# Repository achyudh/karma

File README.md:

# Karma

Karma is a 36-key wireless split ergonomic mechanical keyboard inspired by two very popular ergonomic keyboards: [Corne](https://github.com/foostan/crkbd) and [TOTEM](https://github.com/GEIGEIGEIST/TOTEM).

## Features

- **Ergonomic 36-key layout**: A compact layout with 3x5 column-staggered keys, plus 3 thumb keys for each side.
- **Wireless first**: Prioritizes a wireless split setup but can be used partially-wired by connecting the central side using USB-C.
- **Low-profile design**: Engineered for a sleek, low-profile build that allows your palms to rest comfortably on the table while typing. This is achieved through the use of Kailh Choc switches and recessed cutouts for hot-swap sockets, reducing the overall case height (similar to the TOTEM keyboard), and using 1mm EVA foam instead of rubber feet.
- **Exceptional battery life**: Has a battery life that is measured in weeks, not days.

### Firmware

The Karma keyboard supports the [ZMK](https://zmk.dev/) open-source firmware. You can find my ZMK configuration for this keyboard in [this repo](https://github.com/achyudh/karma-zmk).

## Build Guide

### Bill of Materials

To build the Karma keyboard, you'll need the following components:

| Part Name                               | Qty    | Remarks   |
| --------------------------------------- |:------:| --------- |
| 2x SEEED XIAO BLE microcontrollers      | 2      |           |
| Kailh Choc V1 low-profile switches      | 36     | Low-profile mechanical switches |
| Keycaps compatible with Kailh Choc V1   | 36     | MX-spaced keycaps are preferred for better fit |
| Hotswap sockets for Kailh Choc V1       | 36     |           |
| SOD123 diodes                           | 36     |           |
| JST PH 2-pin SMD Header                 | 2      |           |
| 301230 LiPo Batteries                   | 2      | Only 1 required for partially wired build |
| 3D-printed case                         | 2      |           |
| M2 screws (5mm length)                  | 8      |           |
| M2 heat-set inserts (2mm height)        | 8      |           |
| Self-adhesive EVA foam (1mm)            | -      | A slimmer alternative to rubber feet |

### Assembly

**1. Order the Components**
- Zip up the gerber files for the [left side](./mk1/pcb-left/pcb-left-gerbers/) and the [right side](./mk1/pcb-right/pcb-right-gerbers/).
- Order the PCBs from a PCB prototype manufacturer like JLCPCB.
- 3D print the STL files for the case in [this repo](./mk1/enclosure/).
- All the other components are generic and can be found in Aliexpress.

**2. Solder the Diodes**
- Solder the SOD123 diodes to the top of the PCB, paying attention to the polarity.
- Apply solder to one pad, place the diode, and reflow the solder. Then solder the second pad.

**3. Install the Hotswap Sockets**
- Solder hotswap sockets in place by first securing one pad, then ensuring they are properly seated before soldering the second pad.

**4. Microcontroller Installation**
- Flash the firmware onto the SEEED XIAO BLE microcontrollers before soldering them to the PCB.
- Place the microcontroller in the designated spot and solder the pads, starting with the corners to secure it, then solder the rest.

**5. Connect the Batteries**
- Solder the JST PH 2-pin SMD Header to the PCB.
- Check the polarity of the battery with a multimeter and connect the batteries to the JST header such that the red wire is connected to the positive (+) pad and the black wire to the negative (-) pad on the PCB.

**6. Mount the Case**
- Insert M2 heat-set inserts into the screw holes in the 3D-printed case.
- Place the PCB inside the case, ensuring the microcontroller and battery fit snugly.
- Attach the two halves of the case using the M2 screws, securing them tightly.

**7. Install the Keycaps and Switches**
- Insert the Kailh Choc V1 switches into the hotswap sockets, ensuring they click into place.
- Attach your keycaps to the switches.

**8. Add EVA Foam**
- Cut and apply self-adhesive EVA foam to the bottom of the case for added grip and cushioning.

**9. Final steps**
- Once assembled, test the keyboard to ensure all switches and connections work.
- If necessary, adjust the [ZMK](https://zmk.dev/) firmware for your specific keymap.

Congratulations! You've completed your Karma keyboard build.

## License

This project is open-source and licensed under the CERN Open Hardware Licence Version 2 - Strongly Reciprocal License. See the [LICENSE](./LICENSE) file for details.

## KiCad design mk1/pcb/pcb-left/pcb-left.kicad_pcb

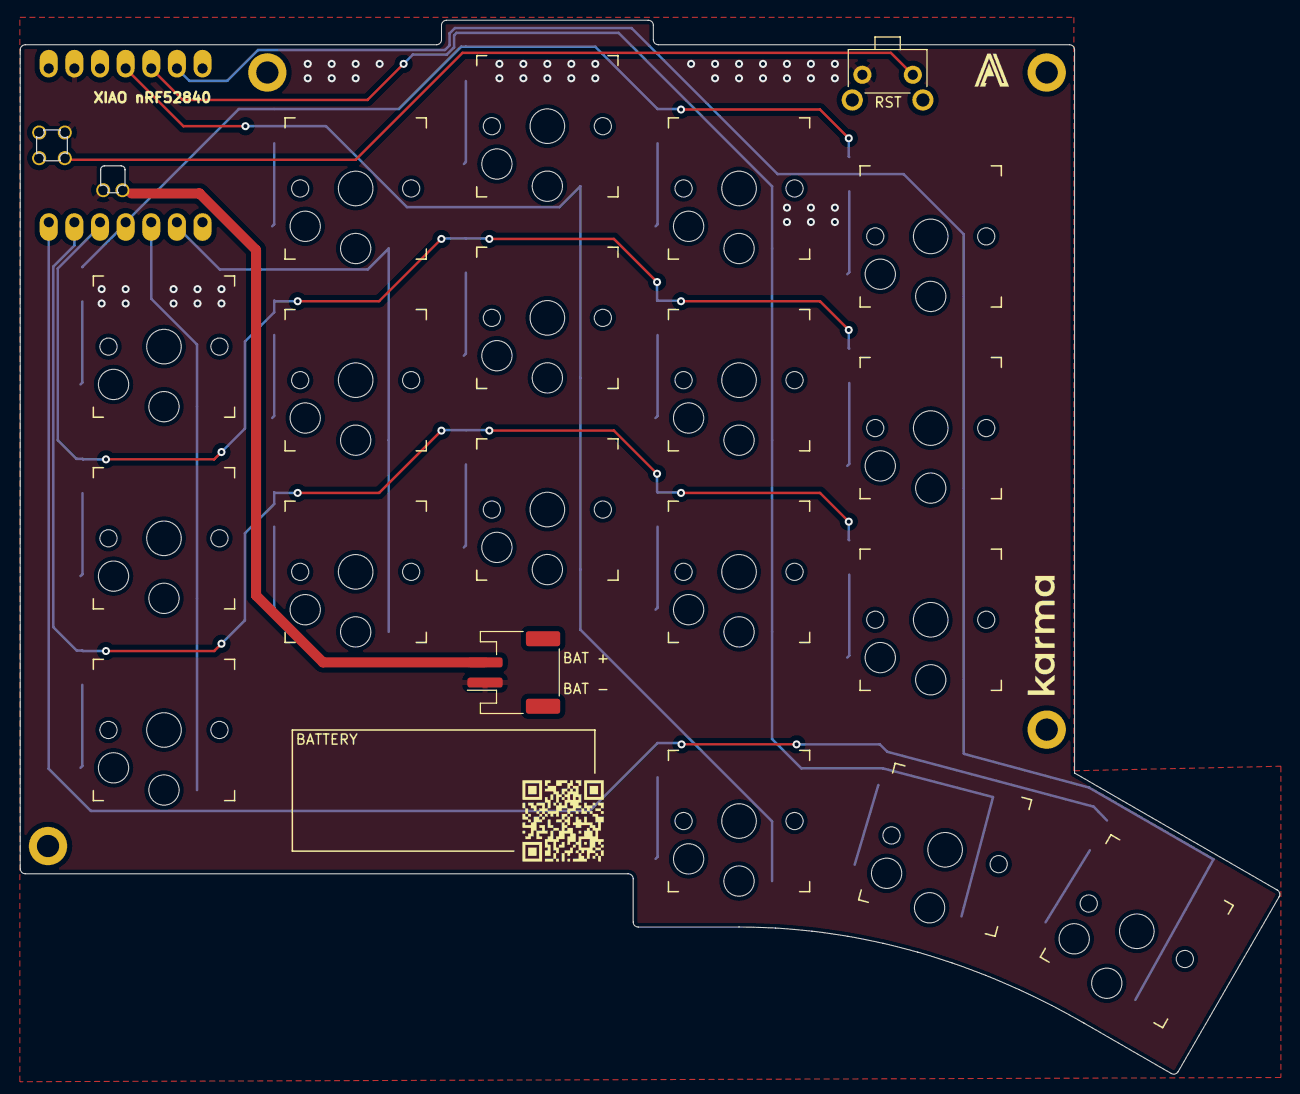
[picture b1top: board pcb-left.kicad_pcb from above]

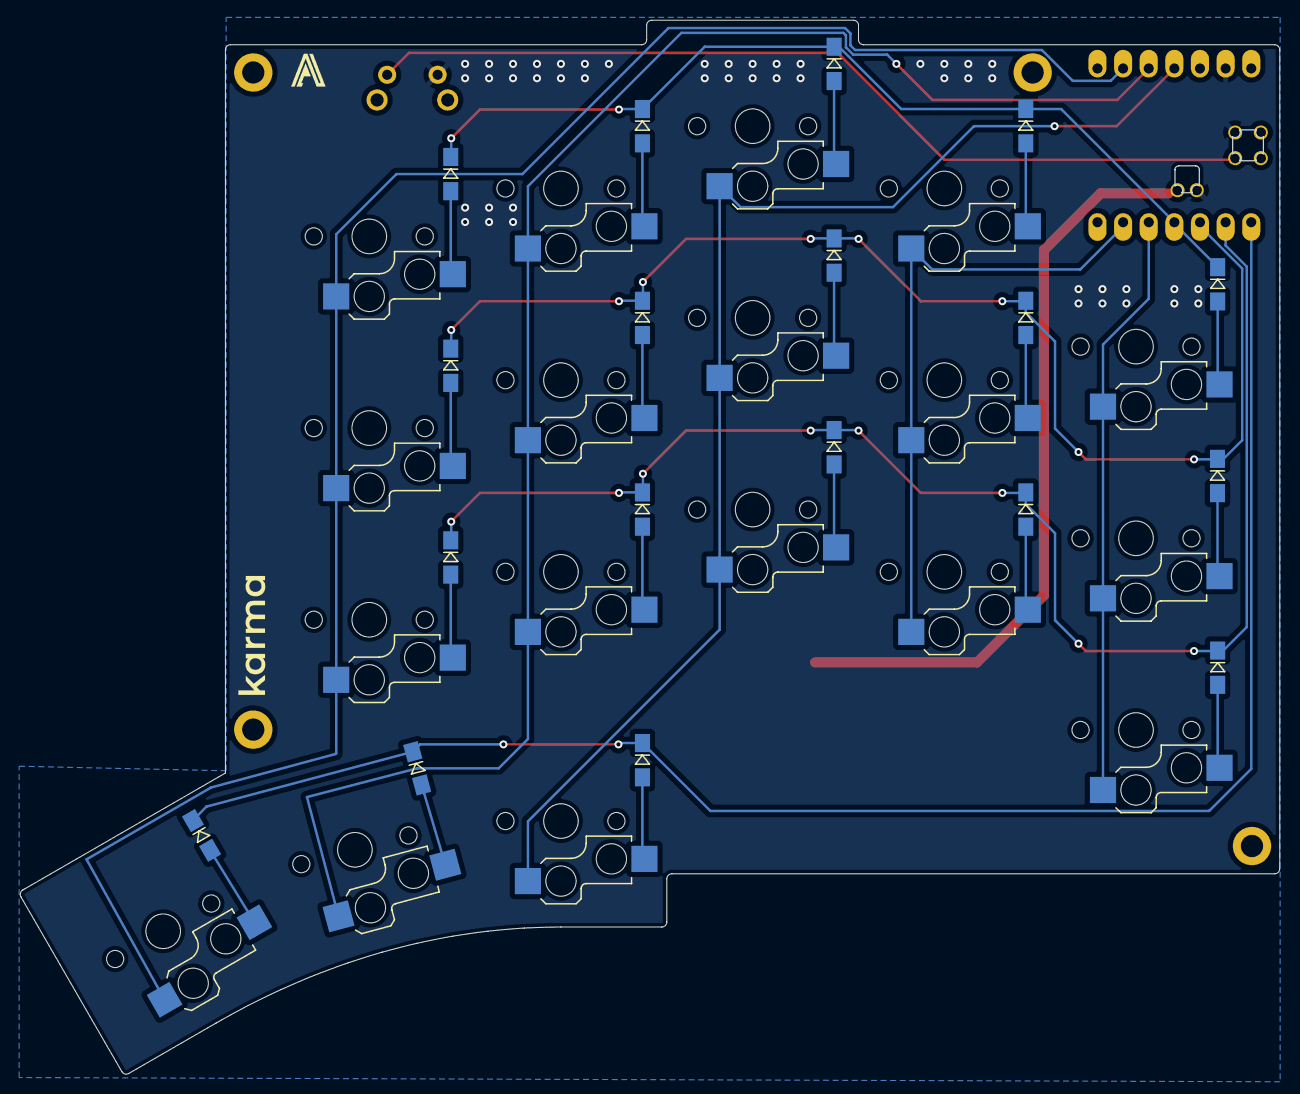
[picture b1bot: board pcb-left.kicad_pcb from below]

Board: 2 copper layers, 124.8 x 104.5 mm, 39 parts (18 on the bottom side), 30 nets.

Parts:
DL1, DL2, DL3, DL4, DL5, DL6, DL7, DL8, DL9, DL10, DL11, DL12, DL13, DL14, DL15, DL16, DL17, DL18: D_Small; Diode_SOD123
J1: BAT; JST_PH_S2B-PH-SM4-TB_1x02-1MP_P2.00mm_Horizontal
RSW1: SW_Push; SKHLLCA010
SWL1, SWL2, SWL3, SWL4, SWL5, SWL6, SWL7, SWL8, SWL9, SWL10, SWL11, SWL12, SWL13, SWL14, SWL15, SWL16, SWL17, SWL18: SW_Push_45deg; Kailh_Socket_PG1350_Optional
U1: xiao-ble; XIAO_nRF52840_SMD_Cutout

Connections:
COL0_L: SWL1.1, SWL6.1, SWL11.1, U1.5 (A8_SDA/0.04_H)
COL1_L: SWL2.1, SWL7.1, SWL12.1, U1.6 (A9_SCL/0.05_H)
COL2_L: SWL3.1, SWL8.1, SWL13.1, SWL16.1, U1.11 (A6_MOSI/1.15)
COL3_L: SWL4.1, SWL9.1, SWL14.1, SWL17.1, U1.10 (A5_MISO/1.14)
COL4_L: SWL5.1, SWL10.1, SWL15.1, SWL18.1, U1.9 (A7_SCK/1.13)
GND_L: J1.1, RSW1.2, U1.13 (GND), U1.18 (GND), U1.20 (GND)
unnamed: DL1.2 (A), SWL1.2
unnamed: DL2.2 (A), SWL2.2
unnamed: DL3.2 (A), SWL3.2
unnamed: DL4.2 (A), SWL4.2
unnamed: DL5.2 (A), SWL5.2
unnamed: DL6.2 (A), SWL6.2
unnamed: DL7.2 (A), SWL7.2
unnamed: DL8.2 (A), SWL8.2
unnamed: DL9.2 (A), SWL9.2
unnamed: DL10.2 (A), SWL10.2
unnamed: DL11.2 (A), SWL11.2
unnamed: DL12.2 (A), SWL12.2
unnamed: DL13.2 (A), SWL13.2
unnamed: DL14.2 (A), SWL14.2
unnamed: DL15.2 (A), SWL15.2
unnamed: DL16.2 (A), SWL16.2
unnamed: DL17.2 (A), SWL17.2
unnamed: DL18.2 (A), SWL18.2
RESET_L: RSW1.1, U1.17 (RESET)
ROW0_L: DL1.1 (K), DL2.1 (K), DL3.1 (K), DL4.1 (K), DL5.1 (K), U1.4 (A11/0.29)
ROW1_L: DL6.1 (K), DL7.1 (K), DL8.1 (K), DL9.1 (K), DL10.1 (K), U1.3 (A10/0.28)
ROW2_L: DL11.1 (K), DL12.1 (K), DL13.1 (K), DL14.1 (K), DL15.1 (K), U1.2 (A4/0.03_H)
ROW3_L: DL16.1 (K), DL17.1 (K), DL18.1 (K), U1.1 (A2/0.02_H)
VBAT_L: J1.2, U1.19 (BAT)

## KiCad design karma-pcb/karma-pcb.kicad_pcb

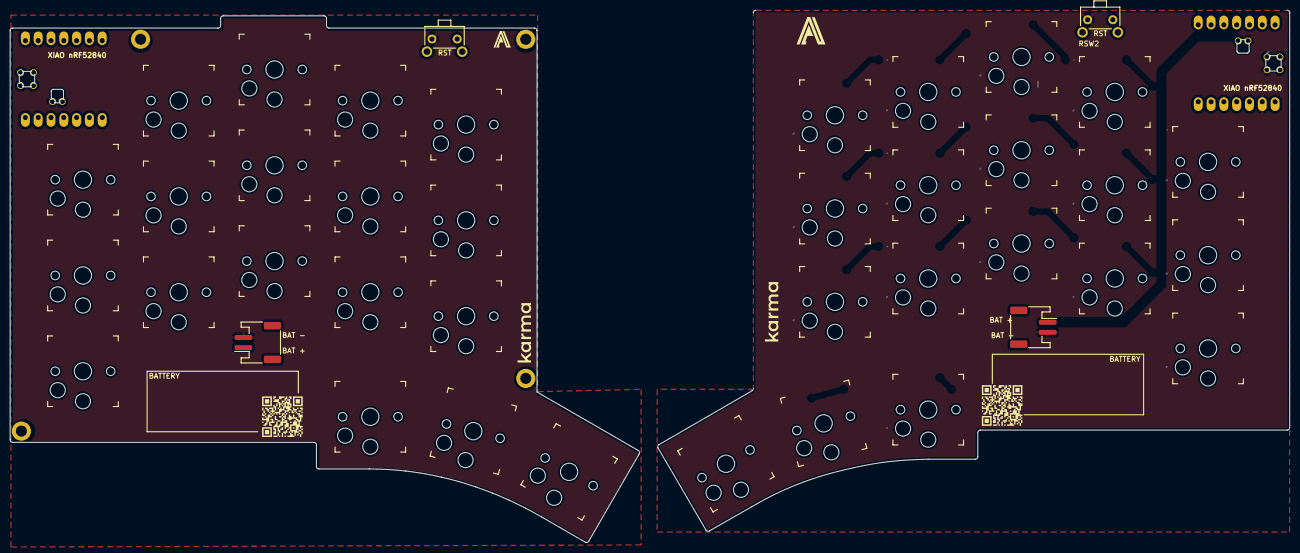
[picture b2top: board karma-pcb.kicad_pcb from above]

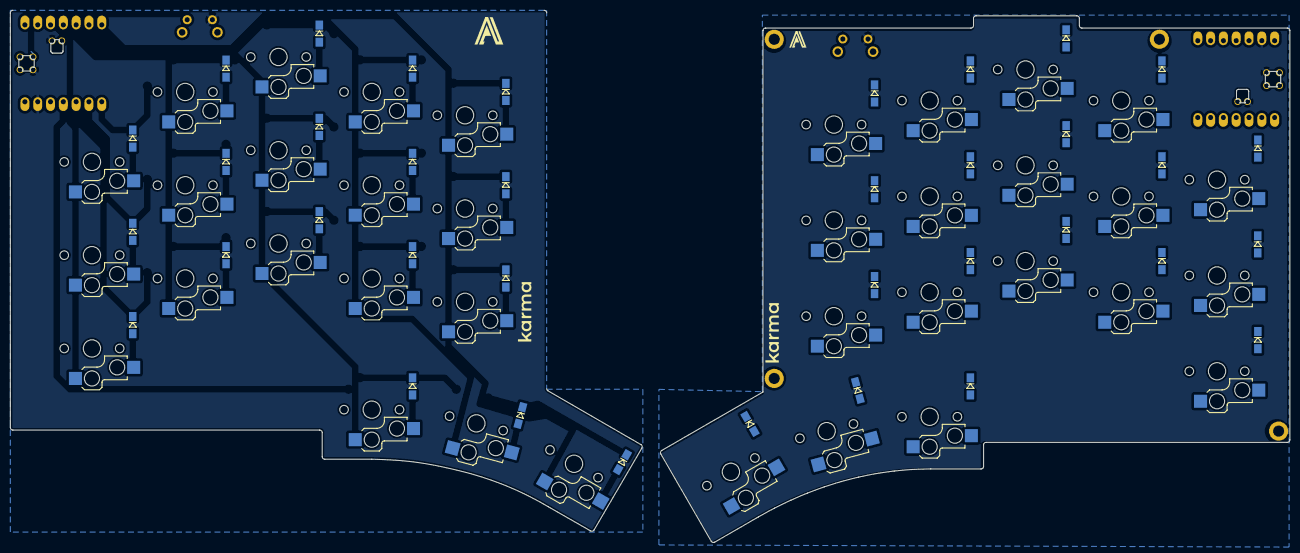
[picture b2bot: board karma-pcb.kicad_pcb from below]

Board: 2 copper layers, 253.8 x 105.6 mm, 78 parts (36 on the bottom side), 60 nets.

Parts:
DL1, DL2, DL3, DL4, DL5, DL6, DL7, DL8, DL9, DL10, DL11, DL12, DL13, DL14, DL15, DL16, DL17, DL18: D_Small; Diode_SOD123
DR1, DR2, DR3, DR4, DR5, DR6, DR7, DR8, DR9, DR10, DR11, DR12, DR13, DR14, DR15, DR16, DR17, DR18: D_Small; Diode_SOD123
J1, J2: BAT; JST_PH_S2B-PH-SM4-TB
RSW1, RSW2: SW_Push; SKHLLCA010
SWL1, SWL2, SWL3, SWL4, SWL5, SWL6, SWL7, SWL8, SWL9, SWL10, SWL11, SWL12, SWL13, SWL14, SWL15, SWL16, SWL17, SWL18: SW_Push_45deg; Kailh_Socket_PG1350_Optional
SWR1, SWR2, SWR3, SWR4, SWR5, SWR6, SWR7, SWR8, SWR9, SWR10, SWR11, SWR12, SWR13, SWR14, SWR15, SWR16, SWR17, SWR18: SW_Push_45deg; Kailh_Socket_PG1350_Optional
U1, U2: xiao-ble; XIAO_nRF52840_SMD_Cutout

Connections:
COL0_L: SWL1.1, SWL6.1, SWL11.1, U1.5 (A8_SDA/0.04_H)
COL0_R: SWR5.1, SWR10.1, SWR15.1, U2.3 (A10/0.28)
COL1_L: SWL2.1, SWL7.1, SWL12.1, U1.6 (A9_SCL/0.05_H)
COL1_R: SWR4.1, SWR9.1, SWR14.1, U2.4 (A11/0.29)
COL2_L: SWL3.1, SWL8.1, SWL13.1, SWL16.1, U1.11 (A6_MOSI/1.15)
COL2_R: SWR3.1, SWR8.1, SWR13.1, SWR18.1, U2.5 (A8_SDA/0.04_H)
COL3_L: SWL4.1, SWL9.1, SWL14.1, SWL17.1, U1.10 (A5_MISO/1.14)
COL3_R: SWR2.1, SWR7.1, SWR12.1, SWR17.1, U2.6 (A9_SCL/0.05_H)
COL4_L: SWL5.1, SWL10.1, SWL15.1, SWL18.1, U1.9 (A7_SCK/1.13)
COL4_R: SWR1.1, SWR6.1, SWR11.1, SWR16.1, U2.7 (B8_TX/1.11)
GND_L: J1.2, RSW1.2, U1.13 (GND), U1.18 (GND), U1.20 (GND)
GND_R: J2.2, RSW2.2, U2.13 (GND), U2.18 (GND), U2.20 (GND)
unnamed: DL1.2 (A), SWL1.2
unnamed: DL2.2 (A), SWL2.2
unnamed: DL3.2 (A), SWL3.2
unnamed: DL4.2 (A), SWL4.2
unnamed: DL5.2 (A), SWL5.2
unnamed: DL6.2 (A), SWL6.2
unnamed: DL7.2 (A), SWL7.2
unnamed: DL8.2 (A), SWL8.2
unnamed: DL9.2 (A), SWL9.2
unnamed: DL10.2 (A), SWL10.2
unnamed: DL11.2 (A), SWL11.2
unnamed: DL12.2 (A), SWL12.2
unnamed: DL13.2 (A), SWL13.2
unnamed: DL14.2 (A), SWL14.2
unnamed: DL15.2 (A), SWL15.2
unnamed: DL16.2 (A), SWL16.2
unnamed: DL17.2 (A), SWL17.2
unnamed: DL18.2 (A), SWL18.2
unnamed: DR1.2 (A), SWR1.2
unnamed: DR2.2 (A), SWR2.2
unnamed: DR3.2 (A), SWR3.2
unnamed: DR4.2 (A), SWR4.2
unnamed: DR5.2 (A), SWR5.2
unnamed: DR6.2 (A), SWR6.2
unnamed: DR7.2 (A), SWR7.2
unnamed: DR8.2 (A), SWR8.2
unnamed: DR9.2 (A), SWR9.2
unnamed: DR10.2 (A), SWR10.2
unnamed: DR11.2 (A), SWR11.2
unnamed: DR12.2 (A), SWR12.2
unnamed: DR13.2 (A), SWR13.2
unnamed: DR14.2 (A), SWR14.2
unnamed: DR15.2 (A), SWR15.2
unnamed: DR16.2 (A), SWR16.2
unnamed: DR17.2 (A), SWR17.2
unnamed: DR18.2 (A), SWR18.2
RESET_L: RSW1.1, U1.17 (RESET)
RESET_R: RSW2.1, U2.17 (RESET)
ROW0_L: DL1.1 (K), DL2.1 (K), DL3.1 (K), DL4.1 (K), DL5.1 (K), U1.4 (A11/0.29)
ROW0_R: DR1.1 (K), DR2.1 (K), DR3.1 (K), DR4.1 (K), DR5.1 (K), U2.8 (B9_RX/1.12)
ROW1_L: DL6.1 (K), DL7.1 (K), DL8.1 (K), DL9.1 (K), DL10.1 (K), U1.3 (A10/0.28)
ROW1_R: DR6.1 (K), DR7.1 (K), DR8.1 (K), DR9.1 (K), DR10.1 (K), U2.9 (A7_SCK/1.13)
ROW2_L: DL11.1 (K), DL12.1 (K), DL13.1 (K), DL14.1 (K), DL15.1 (K), U1.2 (A4/0.03_H)
ROW2_R: DR11.1 (K), DR12.1 (K), DR13.1 (K), DR14.1 (K), DR15.1 (K), U2.10 (A5_MISO/1.14)
ROW3_L: DL16.1 (K), DL17.1 (K), DL18.1 (K), U1.1 (A2/0.02_H)
ROW3_R: DR16.1 (K), DR17.1 (K), DR18.1 (K), U2.11 (A6_MOSI/1.15)
VBAT_L: J1.1, U1.19 (BAT)
VBAT_R: J2.1, U2.19 (BAT)

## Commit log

2023-04-03 Create LICENSE
2023-04-05 Add karmalib.pretty
2023-04-05 Add .gitignore
2023-04-05 Add karma schema rev 0.1
2023-04-08 Add left side pcb design rev 0.1
2023-04-11 Fix board edge DRC failures on the left side
2023-04-11 Fix board edge DRC failures on the right side
2023-04-11 Fix positioning of the controller on the right pcb
2023-04-12 Improve trace routing
2023-04-12 Add 3D models to karmalib.pretty
2023-04-14 Update Kailh PG1350 footprint to be hotswap only
2023-04-14 Add via stitching
2023-04-15 Add silkscreen labels
2023-04-15 Add silkscreen label for controller
2023-04-17 Add 3D model for keycaps
2023-05-08 Split karma-pcb into pcb-left and pcb-right
2023-05-11 Align mounting holes in left-pcb
2023-05-26 Fix DRC issues in left-pcb
2023-05-26 Fix DRC issues in right-pcb
2023-05-26 Update 3d models for right-pcb
2023-05-27 Update step models for left-pcb and right-pcb
2023-05-27 Add enclosure stl files
2023-05-28 Rename project directories
2023-05-28 Remove compressed gerber files
2023-06-19 Fix microcontroller placement
2024-03-06 Add pcb and enclosure images for documentation
2024-03-06 Add pcb schematics for documentation
2024-10-15 enclosure: Add step files
2025-08-09 mk1: move pcb and enclosure
2025-11-08 enclosure: add no-logo variants
2025-11-26 docs: change cover
2026-02-08 mk1: move existing files to mk1
2026-02-10 mk1/pcb: consolidate KiCad files
2026-02-25 mk1/pcb-left: add power switch and debug header, update reset button
2026-03-15 mk1/pcb: revert pcb-left to earlier version
